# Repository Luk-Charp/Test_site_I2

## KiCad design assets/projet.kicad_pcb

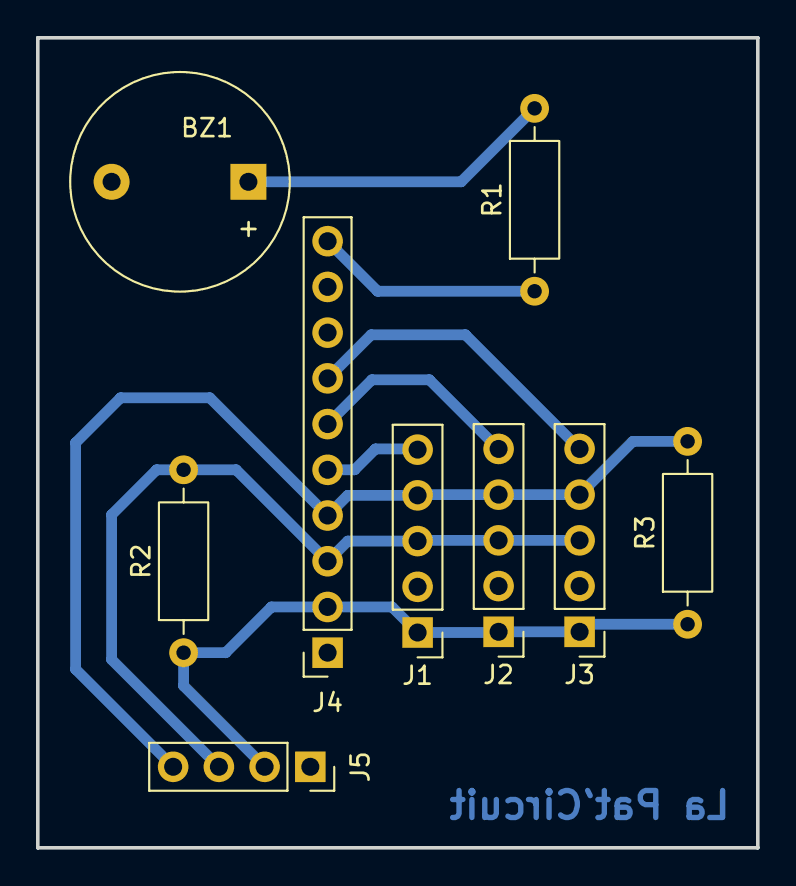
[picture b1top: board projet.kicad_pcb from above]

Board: 2 copper layers, 40.0 x 45.0 mm, 9 parts (0 on the bottom side), 9 nets.

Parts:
BZ1: Buzzer; Buzzer_12x9.5RM7.6
J1, J2, J3: Conn_01x05; PinHeader_1x05_P2.54mm_Vertical
J4: Conn_01x10; PinSocket_1x10_P2.54mm_Vertical
J5: Conn_01x04; PinSocket_1x04_P2.54mm_Vertical
R1: 220; R_Axial_DIN0207_L6.3mm_D2.5mm_P10.16mm_Horizontal
R2, R3: R; R_Axial_DIN0207_L6.3mm_D2.5mm_P10.16mm_Horizontal

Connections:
GND: BZ1.2 (-), J1.2, J2.2, J3.2, J4.1, J5.1
GPIO 0_1: J1.5, J4.5
GPIO 0_2: J2.5, J4.6
GPIO 0_3: J3.5, J4.7
unnamed: BZ1.1 (+), R1.2
unnamed: J4.10, R1.1
SCL: J1.4, J2.4, J3.4, J4.4, J5.4, R3.2
SDA: J1.3, J2.3, J3.3, J4.3, J5.3, R2.2
VIN: J1.1, J2.1, J3.1, J4.2, J5.2, R2.1, R3.1

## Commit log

2026-02-16 Fix HTML formatting and structure
2026-02-16 Refactor CSS styles and structure
2026-02-16 Fix HTML encoding issues in index.html
2026-02-16 Refactor CSS styles and restore imports
2026-02-24 Refactor index.html structure and content
2026-02-24 Refactor CSS styles and improve responsiveness
2026-03-03 Refactor CSS for improved structure and responsiveness
2026-04-03 changement portfolio
2026-04-03 retour
2026-04-03 essai
